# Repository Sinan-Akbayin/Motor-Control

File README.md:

# Motor-Control

KiCad hardware design for a three-phase BLDC motor drive, built around an STM32G473 microcontroller and a DRV8350S gate driver.

> **Status:** version 1.0.0. The schematic is finished (ERC: 0 errors) and the PCB is placed and routed (DRC: 0 errors, 0 unconnected items). No board has been built or tested yet. See [Known issues and open items](#known-issues-and-open-items).

The full schematic is also available as a PDF, so it can be viewed without KiCad: [docs/schematic.pdf](docs/schematic.pdf). In most PDF viewers you can click a sheet symbol to open that sheet.

To edit the design, open `BLDC_V_0.1/BLDC_V_0.1.kicad_pro` in KiCad 10 or newer. The `BLDC_V_0.1` file and folder names are kept from the upstream repository; they do not give the version. This repository holds the hardware design only; no firmware is included.

## Hardware overview

| Block | Parts | Notes |
|---|---|---|
| MCU | STM32G473VET6 | LQFP100, 24 MHz crystal |
| Gate driver | DRV8350S | SPI interface and enable line to the MCU; nFAULT goes to the TIM8 break input |
| Power stage | 6 × BSC070N10NS5SCATMA1 N-channel MOSFETs (PG-WSON-8) | Three half-bridges, 5 Ω gate resistors |
| Current sensing | 4 × AD8418A, 3 × 1.5 mΩ phase shunts, 1 × 1 mΩ DC bus shunt | Phase shunts between each half-bridge and its motor phase; bus shunt on the high side |
| Voltage sensing | 39 kΩ / 2.2 kΩ dividers | DC bus and all three phases |
| DC bus input | 30 A 58 VDC ATO fuse, 5.0SMDJ58A TVS (5 kW) | Overcurrent and overvoltage protection for a 48 V nominal bus |
| DC bus capacitors | 6 × Rubycon 100ZLJ220M12.5X25 (220 µF, 100 V, through-hole) | 1320 µF in total; together they carry about 12 A RMS of ripple current at 20 kHz, enough for 15 A RMS phase current |
| Power supply | LMR38020 buck, AMS1117-3.3 regulator | DC bus to 5 V, then 5 V to 3.3 V; a BAT54C diode-OR feeds the 3.3 V regulator from the 5 V rail or USB VBUS, so USB alone can power the 3.3 V logic (with little voltage margin, see changes.md) |
| CAN | ISO1050 isolated transceiver, B0505S-1WR2 isolated 5 V converter | ACM2012 choke and PESD2CAN ESD protection; a 240 Ω resistor gives the converter its minimum load |
| USB | Micro-B connector, USBLC6-2SC6 | ESD protection on D+ and D- |
| Temperature sensing | 10 kΩ NTC | On the board, plus an input for an external sensor on J10 |
| PCB | — | 4 copper layers, 98.5 × 84.3 mm, 1.6 mm thick (see [PCB](#pcb)) |

## Theoretical specifications

These values are calculated from datasheets. They have not been measured on a board yet. The design point is a 48 V bus, 20 kHz PWM, 40 °C ambient air and a MOSFET junction temperature of at most 110 °C.

| Parameter | Value | What limits it |
|---|---|---|
| Nominal input voltage | 48 V (13-cell Li-ion pack, 54.6 V when fully charged) | — |
| Input voltage range | 9 V to 58 V | Low end: DRV8350S supply, 9 V minimum. High end: the 58 V stand-off voltage of the TVS diode D5; above about 64 V the TVS starts to conduct |
| Absolute maximum bus voltage | 80 V, short transients only | DRV8350S VM pin (80 V absolute maximum) and AD8418A inputs (80 V survival). These are damage limits, not operating limits: the DRV8350S is specified up to 75 V and the AD8418A up to 70 V. At 80 V the bus voltage divider would also put 4.27 V on the MCU pin, above its 3.3 V supply |
| Continuous phase current | 15 A RMS without a heatsink (estimate, to be confirmed by a thermal test) | MOSFET heating: about 1.4 W per MOSFET with 50 K/W junction-to-air. The datasheet gives 50 K/W for a single MOSFET on a test board with 6 cm² of copper; six MOSFETs close together on this board may run hotter |
| Continuous phase current with a heatsink | about 18 A RMS | DC bus capacitor ripple current: 6 × 2.21 A at 100 kHz, about 12.2 A at 20 kHz |
| Peak phase current (short pulses) | ±50 A | Range of the phase current measurement. ±50 A gives 0.15 V to 3.15 V at the ADC; the motor-control firmware (not part of this repository) must set the over-current trip below this |
| DC input current | about 17 A at 15 A RMS phase current | 30 A fuse |
| Output power | about 0.8 kW at 48 V and 15 A RMS | Assumes space-vector PWM at full modulation, a power factor of 0.9, and no losses. With plain sine PWM it is about 0.7 kW |
| PWM frequency | 20 kHz (design point used for the numbers above) | Higher frequencies raise MOSFET switching losses |
| Phase current measurement | 30 mV/A, 1.65 V at 0 A, range about ±53 A | 1.5 mΩ shunt × AD8418A gain of 20. The ideal range is ±55 A (0 V to 3.3 V); the amplifier output cannot reach the supply rails exactly |
| DC bus current measurement | 20 mV/A, 1.65 V at 0 A, range about ±80 A | 1 mΩ shunt × AD8418A gain of 20 (ideal ±82.5 A) |
| DC bus voltage measurement | 0 V to 61.8 V for 0 V to 3.3 V at the ADC | 39 kΩ / 2.2 kΩ divider |
| Overvoltage clamp | about 80 V or less for surge currents up to about 21 A (rough estimate, not a guaranteed value) | 5.0SMDJ58A datasheet: at most 93.6 V at 53.5 A (10/1000 µs pulse). The datasheet gives no clamping voltage at lower currents |
| Interfaces | Isolated CAN, USB, UART, I2C, SPI, SWD, Hall sensors or encoder | — |

How the main numbers were found:

- **MOSFET heating.** BSC070N10NS5SCATMA1 on-resistance is at most 7.0 mΩ at 25 °C. At about 110 °C it is taken as 1.6 times higher, 11.2 mΩ (an estimate; read the exact factor from the datasheet curve). In a half-bridge, each MOSFET conducts about half of the time. At 15 A RMS one MOSFET loses 15² × 0.0112 / 2 = 1.26 W in conduction and about 0.15 W in switching (assuming 50 ns per switching edge; the real value depends on the gate drive current set in the DRV8350S). 1.4 W × 50 K/W = 70 K, so the junction reaches 40 + 70 = 110 °C.
- **Capacitor ripple.** In a three-phase inverter, the RMS ripple current in the DC bus capacitors can reach about 0.65 times the RMS phase current. At 15 A this is 9.8 A. Each capacitor is rated 2.21 A at 100 kHz and 105 °C (Rubycon ZLJ datasheet). At 20 kHz the rating is about 8 % lower, so six capacitors carry 6 × 2.21 × 0.92 ≈ 12.2 A.
- **TVS clamp.** At its rated pulse (53.5 A) the 5.0SMDJ58A clamps at 93.6 V. Its breakdown voltage is at most 71.2 V, measured at only 1 mA. Drawing a straight line between these two points gives a dynamic resistance is about (93.6 − 71.2) / 53.5 ≈ 0.42 Ω. The clamp stays at or below 80 V while the surge current is at most (80 − 71.2) / 0.42 ≈ 21 A. The real clamping curve is not a straight line, so this is only a rough estimate and not a guaranteed limit; check the protection against the surge waveform expected in use.

## Connectors

| Ref | Function |
|---|---|
| J14, J4 | DC bus power pads: VDC_IN (before the fuse) and GND |
| J5, J6, J7 | Motor phase pads: A, B and C |
| J13 | CAN bus: 1 CAN_H, 2 CAN_L, 3 isolated ground through 10 Ω |
| J12 | Jumper for the 120 Ω CAN termination: fit it across pins 2 and 3 (pin 1 is not connected) |
| J10 | 6-pin JST-EH for Hall sensors or an encoder (one at a time): 1 +5 V, 2 HA/A, 3 HB/B, 4 HC/Z (index), 5 external NTC, 6 GND |
| J2 | 10-pin SWD header with SWO and NRST |
| J1 | USB Micro-B |
| J3 | BOOT0 selection |
| J8 | UART, digital output DO_1 |
| J11 | I2C |
| J9 | External SPI |

## MCU pins

| Function | Pins |
|---|---|
| Gate driver high-side inputs A, B, C | PC6, PC7, PC8 |
| Gate driver low-side inputs A, B, C | PC10, PC11, PC12 |
| Gate driver SPI: CS, SCK, MISO, MOSI | PB12, PB13, PB14, PB15 |
| Gate driver enable, fault | PD15, PB7 (TIM8_BKIN) |
| Phase current A, B, C | PA1, PA3, PE7 (fast ADC channels, COMP1/2/4 inputs) |
| DC bus current | PA0 (fast ADC channel, COMP3 input) |
| Phase voltage A, B, C | PE14, PE15, PE13 |
| DC bus voltage | PA8 |
| Temperature: board, external | PC3, PC0 |
| Hall sensors / encoder A, B, C(Z) | PE2, PE3, PE4 (TIM3 CH1–CH3); C(Z) also on PD2 (TIM3_ETR) |
| CAN: RX, TX | PD0, PD1 |
| USB: D-, D+ | PA11, PA12 |
| SWD: SWDIO, SWCLK, SWO | PA13, PA14, PB3 |
| UART: RX, TX | PC4, PC5 |
| Digital output DO_1 | PB0 |
| I2C: SCL, SDA | PA15, PB9 |
| External SPI: CS, SCK, MISO, MOSI | PA4, PA5, PA6, PA7 |
| LEDs: CAN, process | PE5, PE1 |

## PCB

**Size.** 98.5 × 84.3 mm, rounded corners (1 mm radius), four M3 mounting holes. The power pads (DC input and motor phases) are on the bottom edge, the signal connectors on the top edge.

**Layer stack.** 4 copper layers, 1.6 mm total thickness, FR4:

| Layer | Copper | Use |
|---|---|---|
| F.Cu (top) | 70 µm (2 oz) | Parts, signal tracks, power copper areas |
| dielectric | 0.10 mm | — |
| In1.Cu | 35 µm (1 oz) | GND plane (kept out of the isolated CAN side) |
| dielectric (core) | 1.17 mm | — |
| In2.Cu | 35 µm (1 oz) | Power planes: VDC under the power stage, +5 V under the buck converter, +3.3 V under the MCU |
| dielectric | 0.10 mm | — |
| B.Cu (bottom) | 70 µm (2 oz) | Signal tracks, GND pour, part of the DC input copper |

**Netclasses** (in `BLDC_V_0.1.kicad_pro`; net names are assigned to classes by pattern):

| Netclass | Nets | Track width | Clearance | Via (pad / drill) |
|---|---|---|---|---|
| Default | everything not listed below | 0.20 mm | 0.20 mm | 0.6 / 0.3 mm |
| Power | DC bus, switch nodes, shunt nets | 0.50 mm | 0.25 mm | 0.8 / 0.4 mm |
| GateDrive | gate drive nets (DRV8350S to MOSFET gates) | 0.40 mm | 0.25 mm | 0.6 / 0.3 mm |
| Supply | GND, +5 V, +3.3 V, LDO_IN, VBUS and the converter nets | 0.40 mm | 0.20 mm | 0.6 / 0.3 mm |
| ISO | CAN bus and isolated-side nets | 0.30 mm | 0.20 mm | 0.6 / 0.3 mm |

The high-current paths (DC bus, switch nodes, motor phases) are copper areas, not tracks.

**Board-wide minimums** (board setup in `BLDC_V_0.1.kicad_pro`): track width 0.2 mm, clearance 0.15 mm, smallest hole 0.2 mm (the five thermal vias in the U5 DRV8350S footprint; every other via on the board is 0.6 / 0.3 mm or 0.8 / 0.4 mm), via diameter 0.6 mm, annular ring 0.13 mm (the netclass vias have 0.15 mm or more), hole-to-copper 0.25 mm, hole-to-hole 0.25 mm, copper-to-board-edge 0.3 mm. The custom rule file `BLDC_V_0.1.kicad_dru` lowers the pad-to-pad clearance to 0.15 mm only between pads of the same part, for U1 (MCU, 0.5 mm pin pitch, 0.195 mm between pads) and C28 (0201 capacitor, 0.18 mm between pads); the netclass clearances apply everywhere else.

## Fabrication outputs

Gerber, drill, BOM and position files are not in the repository. Generate them from `BLDC_V_0.1.kicad_pcb` in KiCad (*File → Fabrication Outputs*), and refill the copper areas (*Edit → Fill All Zones*) first.

## Known issues and open items

- The board has not been built or tested. All ratings above are calculated, not measured.
- The CAN isolation is functional isolation, not safety isolation. The isolating parts themselves have only about 0.9 mm between their pins, and the ground copper areas keep at least 2.6 mm from the isolated side (the closest other copper, a +5 V track, is 2.36 mm away). Do not rely on it to protect people from dangerous voltages.
- DRC reports 0 errors and 13 warnings. 3 are silkscreen warnings caused by footprint graphics. 10 say that a board footprint differs from its library copy (R15, R16, R20, R21, R25, R26, L3, U2, U4 and J1); the difference is 1 nm rounding in pads or graphics.
- The 3D body of F1 (fuse holder) is a close substitute, not the real part.
- Confirm the PCB stack-up with the intended fabricator.
- Check the TVS, MOSFET and capacitor numbers against the manufacturers' current datasheets before relying on them.
- The 3.3 V rail has little voltage margin. The AMS1117-3.3 (U2) needs at least 4.6 V at its input, but its input comes from +5 V or USB VBUS through the BAT54C diode D2, so in the worst case it gets only 4.2 to 4.5 V and the 3.3 V rail can sag. With typical part values the margin is about 0.25 V. Details in [changes.md](changes.md#power-supply).
- The isolated CAN supply can be slightly too high. The isolated converter U9 (B0505S-1WR2) is unregulated; with its minimum load it gives 5.25 V typical and up to 5.5 V worst case. The ISO1050 (U10) is specified for 4.75 to 5.25 V on VCC2, with 6 V absolute maximum. Measure VCC2 on the first board with the CAN bus idle. Details in [changes.md](changes.md#isolated-can).
- The TVS cannot absorb braking energy. If the battery is disconnected while the motor brakes, the bus voltage rises, so the motor-control firmware must limit or stop braking when the bus voltage gets too high.
- Local bus decoupling has not been tested. Each half-bridge has three ceramic capacitors from VDC to GND, 15 nF, 330 nF and 1 µF (C39, C40 and C42 on phase A), 5 to 9 mm from the MOSFETs (centre to centre). That is about 1.35 µF per phase. On the first board, measure the ringing on the switch nodes; if it is too high, add 100 V ceramic capacitance close to the MOSFETs.

## Repository layout

All design files are in [BLDC_V_0.1/](BLDC_V_0.1):

| File | Content |
|---|---|
| `BLDC_V_0.1.kicad_pro` | Main KiCad project file, including the netclasses and board design rules |
| `BLDC_V_0.1.kicad_sch` | Top-level schematic |
| `MCU_STM32.kicad_sch` | MCU, power pins, programming and USB |
| `DRV8350.kicad_sch` | Gate driver, buck converter, bulk capacitors, temperature and voltage measurement |
| `DC_Bus.kicad_sch` | DC bus input: fuse, TVS, bus current shunt and amplifier |
| `Half-Bridge.kicad_sch` | One half-bridge with its current and voltage sensing, used three times |
| `Communications.kicad_sch` | Connectors, isolated CAN, ESD protection |
| `BLDC_V_0.1.kicad_pcb` | PCB layout |
| `BLDC_V_0.1.kicad_dru` | Custom design rule (fine-pitch pad clearance, see [PCB](#pcb)) |
| `Libraries/` | Third-party symbols, footprints and 3D models |
| `BLDC_Project.pretty/` | Project footprint library: the 10 × 10 mm power pads, the MOSFET footprint (`Infineon_PG-WSON-8_BSC070N10NS5SC`) and the DRV8350S footprint (`TI_RTV0032E_DRV8350S`) |

Outside `BLDC_V_0.1/`:

| Path | Content |
|---|---|
| `docs/schematic.pdf` | The whole schematic as a PDF with clickable sheet links, exported from KiCad (*File → Plot*); export it again after any schematic change |
| `docs/render/` | 3D renders of the board used in this README |
| `changes.md` | Every change made since the upstream design, with the reason for each one |

The KiCad design files are written by KiCad 10.0. Open them with KiCad 10 or newer.

## Changes from version 0.1

Version 1.0.0 fixes errors in the version 0.1 schematic and replaces the PCB layout. In short:

- Power rails fixed: the 3.3 V rail was split across two unconnected nets, and the buck converter had no feedback.
- USB VBUS separated from the 5 V rail; a diode-OR lets USB power the 3.3 V logic.
- MCU pins reassigned so that the fast ADC channels, comparators, the TIM8 break input and TIM3 (Hall sensors or encoder) can be used.
- New DC bus input: fuse, larger TVS, bus current measurement. Bulk capacitors changed to 100 V parts with enough ripple current rating.
- Isolated CAN corrected (bus capacitors, minimum load for the isolated converter); Hall/encoder connector given supply pins.
- All parts renumbered, so the reference designators do not match the upstream schematic.
- PCB redone from scratch: 4 layers, new outline, placed and routed by script.

[changes.md](changes.md) lists every change and the reason for it.

## Licence

Copyright Sinan Akbayin 2023.

The design files are licensed under the CERN Open Hardware Licence Version 2 - Permissive ([CERN-OHL-P-2.0](LICENSE)). The design is provided without any warranty.

Source location: <https://github.com/Sinan-Akbayin/Motor-Control>

The contents of `BLDC_V_0.1/Libraries/` come from third parties and are not covered by this licence. They remain subject to their own licence terms.

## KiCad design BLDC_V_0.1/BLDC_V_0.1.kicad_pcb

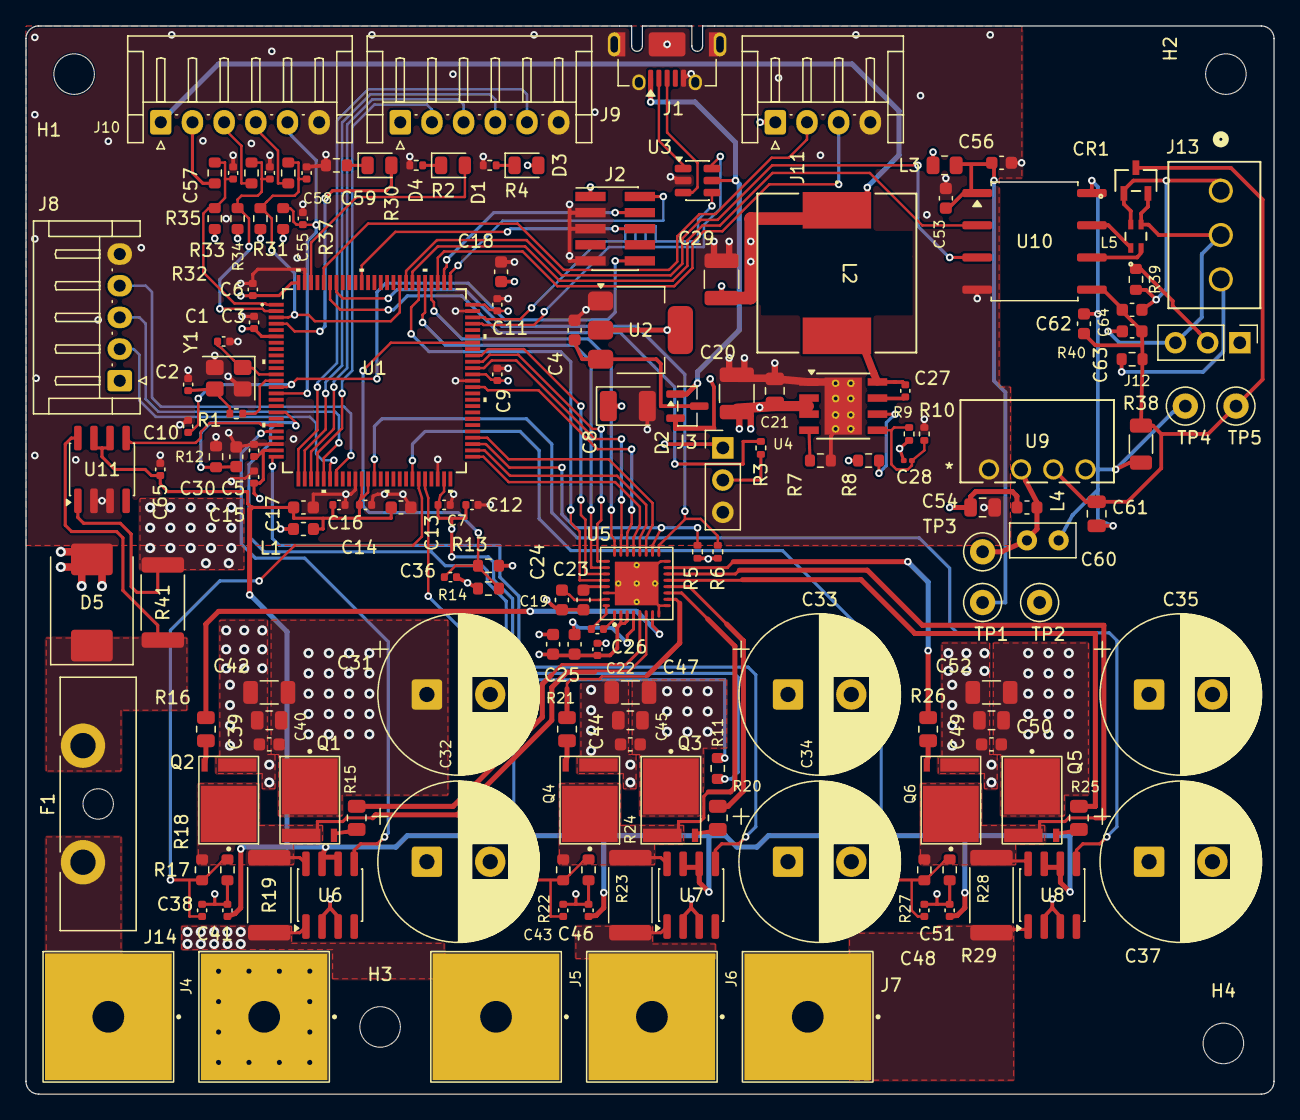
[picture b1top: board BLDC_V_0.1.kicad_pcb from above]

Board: 4 copper layers, 98.5 x 84.3 mm, 159 parts (0 on the bottom side), 104 nets.

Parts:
C1, C2: 20p; C_0402_1005Metric
C3, C5, C6, C7, C9, C10, C11, C12, C14, C15, C16, C22, C27, C36, C38, C41, C43, C46, C48, C51, C65: 100n; C_0402_1005Metric
C4: 4u7; C_0603_1608Metric
C8: 22u; CP_EIA-3528-21_Kemet-B
C13, C23, C24, C25: 1u; C_0603_1608Metric
C17, C18, C19: 10u; C_0603_1608Metric
C20: 2.2u; C_1210_3225Metric
C21: 100n; C_0805_2012Metric
C26: 47n; C_0402_1005Metric
C28: 56p; C_0201_0603Metric
C29: 47u; C_1210_3225Metric
C30: 2.2u; C_0603_1608Metric
C31, C32, C33, C34, C35, C37: 220u; CP_Radial_D12.5mm_P5.00mm
C39, C44, C49: 15n; C_0603_1608Metric
C40, C45, C50: 330n; C_0805_2012Metric
C42, C47, C52: 1u; C_1206_3216Metric
C53: 10n; C_0603_1608Metric
C54, C61: 2.2u; C_0805_2012Metric
C55, C57, C58, C59: 4.7n; C_0402_1005Metric
C56, C62: 100n; C_0603_1608Metric
C60: 470p; C_Disc_D5.0mm_W2.5mm_P2.50mm
C63, C64: 100p; C_0603_1608Metric
CR1: PESD2CAN_215; SOT23_TO-236AB_NEX
D1: BLUE; LED_0805_2012Metric
D2: BAT54C; SOT-23
D3, D4: RED; LED_0805_2012Metric
D5: 5.0SMDJ58A; D_SMC
F1: 30A 58VDC ATO; Fuseholder_Blade_ATO_Littelfuse_Pudenz_2_Pin
H1, H2, H3, H4: MountingHole; MountingHole_3.2mm_M3
J1: USB_B_Micro; USB_Micro-AB_Molex_47590-0001
J2: SWD; PinHeader_2x05_P1.27mm_Vertical_SMD
J3, J12: Conn_01x03; PinHeader_1x03_P2.54mm_Vertical
J4: GND; Power_Welding_Pad_10x10mm
J5, J6, J7: Phase; Power_Welding_Pad_10x10mm
J8: Conn_01x05; JST_EH_S5B-EH_1x05_P2.50mm_Horizontal
J9: Conn_01x06; JST_EH_S6B-EH_1x06_P2.50mm_Horizontal
J10: HALL/ENC; JST_EH_S6B-EH_1x06_P2.50mm_Horizontal
J11: Conn_01x04; JST_EH_S4B-EH_1x04_P2.50mm_Horizontal
J13: 15EDGVC-3.5-03P-14-00AH; CONN_15EDGVC-3.5-03P-1X_DEG
J14: VDC_IN; Power_Welding_Pad_10x10mm
L1: BLM18PG221SN1D; L_0603_1608Metric
L2: CDRH127/LDNP-470MC; IND_CDRH127&slash_LDNP-470MC_SUM
L3: 0R5; R_0805_2012Metric
L4: 4.7u; L_0603_1608Metric
L5: ACM2012-900-2P-T002; ACM2012_TDK
Q1, Q2, Q3, Q4, Q5, Q6: BSC070N10NS5SCATMA1; Infineon_PG-WSON-8_BSC070N10NS5SC
R1: 47R; R_0402_1005Metric
R2: 1k5; R_0402_1005Metric
R3, R6, R10: 10k; R_0402_1005Metric
R4: 1k; R_0402_1005Metric
R5: 4.7k; R_0402_1005Metric
R7: 64k9; R_0603_1608Metric
R8: 100k; R_0603_1608Metric
R9: 40.2k; R_0402_1005Metric
R11: NTC 10k; R_0603_1608Metric
R12, R31, R32, R33, R34: 10k; R_0603_1608Metric
R13, R17, R22, R27: 39k; R_0603_1608Metric
R14, R18, R23, R28: 2k2; R_0603_1608Metric
R15, R16, R20, R21, R25, R26: 5R; R_0805_2012Metric
R19, R24, R29: 0.0015R; R_2512_6332Metric
R30: 470; R_0603_1608Metric
R35, R36, R37: 100; R_0603_1608Metric
R38: 240; R_1206_3216Metric
R39: 120; R_0603_1608Metric
R40: 10; R_0603_1608Metric
R41: 1m 3W; R_2512_6332Metric
TP1, TP2, TP3, TP4, TP5: TestPoint; TestPoint_Loop_D1.80mm_Drill1.0mm_Beaded
U1: STM32G473VET6; LQFP100-14x14mm
U2: AMS1117-3.3; SOT-223-3_TabPin2
U3: USBLC6-2SC6; SOT-23-6
U4: LMR38020SDDAR; TI_SO-PowerPAD-8_ThermalVias
U5: DRV8350SRTVT; TI_RTV0032E_DRV8350S
U6, U7, U8, U11: AD8418A; SOIC-8_3.9x4.9mm_P1.27mm
U9: B0505S-1WR2; B0505S-1WR2_MNS
U10: ISO1050DUB; SOP-8_6.62x9.15mm_P2.54mm
Y1: 24MHz; Crystal_SMD_3225-4Pin_3.2x2.5mm

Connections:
5V_ISO: C60.2, C61.1, C62.2, R38.1, TP4.1, U9.4, U10.8
+3.3V: C3.1, C5.1, C6.1, C7.1, C8.1, C9.1, C11.1, C12.1, C15.1, C18.1, D3.2, J2.1, J3.1, J8.1, J9.1, J11.1, L1.1, L3.1, R5.1, R6.1, R11.1, R31.1, R32.1, R33.1, R34.1, U1.6, U1.24, U1.49, U1.64, U1.75, U1.100, U2.2
+3.3VA: C13.1, C14.1, C16.1, C17.1, C41.1, C46.1, C51.1, C65.1, L1.2, U1.36, U1.37, U6.6, U6.7, U7.6, U7.7, U8.6, U8.7, U11.6, U11.7
+5V: C28.1, C29.1, C54.1, D2.2, J10.1, L2.1, L4.1, R8.1, R9.1
/Communications/CAN_LED: D4.2, U1.4
/Communications/CAN_RX: U1.82, U10.2
/Communications/CAN_TX: U1.83, U10.3
/Communications/DO_1: J8.4, U1.32
/Communications/EXT_SPI_CS: J9.5, U1.26
/Communications/EXT_SPI_MISO: J9.3, U1.28
/Communications/EXT_SPI_MOSI: J9.2, U1.29
/Communications/EXT_SPI_SCK: J9.4, U1.27
/Communications/HALL_A: C57.1, R32.2, R35.2, U1.1
/Communications/HALL_B: C58.1, R33.2, R36.2, U1.2
/Communications/HALL_C: C59.1, R34.2, R37.2, U1.3, U1.84
/Communications/I2C_SCL: J11.3, U1.78
/Communications/I2C_SDA: J11.2, U1.96
/Communications/TEMP_IN: C55.1, J10.5, R31.2, U1.15
/Communications/UART_1_RX: J8.3, U1.30
/Communications/UART_1_TX: J8.2, U1.31
/DRV8350/DRV_CS: U1.51, U5.21
/DRV8350/DRV_ENABLE: U1.62, U5.22
/DRV8350/FAULT_N: R6.2, U1.94, U5.17
/DRV8350/GHA: R15.1, U5.5
/DRV8350/GHB: R20.1, U5.12
/DRV8350/GHC: R25.1, U5.13
/DRV8350/GLA: R16.1, U5.7
/DRV8350/GLB: R21.1, U5.10
/DRV8350/GLC: R26.1, U5.15
/DRV8350/INHA: U1.65, U5.23
/DRV8350/INHB: U1.66, U5.25
/DRV8350/INHC: U1.67, U5.27
/DRV8350/INLA: U1.79, U5.24
/DRV8350/INLB: U1.80, U5.26
/DRV8350/INLC: U1.81, U5.28
/DRV8350/PCB_TEMP: C30.1, R11.2, R12.1, U1.18
/DRV8350/SENS_VDC: C36.1, R13.1, R14.2, U1.69
/DRV8350/SHA: Q1.S, Q2.D, R17.2, R19.1, U5.6, U6.8
/DRV8350/SHB: Q3.S, Q4.D, R22.2, R24.1, U5.11, U7.8
/DRV8350/SHC: Q5.S, Q6.D, R27.2, R29.1, U5.14, U8.8
/DRV8350/SPI_MISO: R5.2, U1.53, U5.18
/DRV8350/SPI_MOSI: U1.54, U5.19
/DRV8350/SPI_SCK: U1.52, U5.20
BOOT0: R3.2, U1.95
CAN_H: C64.2, CR1.1, J13.1, L5.4, R39.1
CAN_L: C63.1, CR1.2, J12.3, J13.2, L5.3
CURR_A: U1.21, U6.5
CURR_B: U1.25, U7.5
CURR_C: U1.38, U8.5
GND: C1.2, C2.2, C3.2, C4.2, C5.2, C6.2, C7.2, C8.2, C9.2, C10.2, C11.2, C12.2, C13.2, C14.2, C15.2, C16.2, C17.2, C18.2, C19.2, C20.2, C21.2, C22.2, C23.1, C24.1, C29.2, C30.2, C31.2, C32.2, C33.2, C34.2, C35.2, C36.2, C37.2, C38.2, C39.2, C40.2, C41.2, C42.2, C43.2, C44.2, C45.2, C46.2, C47.2, C48.2, C49.2, C50.2, C51.2, C52.2, C53.2, C54.2, C55.2, C56.2, C57.2, C58.2, C59.2, C65.2, D5.2, J1.5, J1.SH, J2.3, J2.5, J2.9, J3.3, J4.1, J8.5, J9.6, J10.6, J11.4, Q2.S, Q4.S, Q6.S, R2.1, R4.1, R7.2, R10.2, R12.2, R14.1, R18.1, R23.1, R28.1, R30.1, TP2.1, U1.23, U1.35, U1.48, U1.63, U1.74, U1.99, U2.1, U3.2, U4.1, U4.9, U5.8, U5.9, U5.16, U5.30, U5.33, U6.2, U6.3, U7.2, U7.3, U8.2, U8.3, U9.1, U10.4, U11.2, U11.3, Y1.2, Y1.4
GND_ISO: C61.2, C62.1, C63.2, C64.1, CR1.3, R38.2, R40.2, TP5.1, U9.3, U10.5
HSE_IN: C1.1, U1.12, Y1.1
HSE_OUT: R1.1, U1.13
I_DC: U1.20, U11.5
LDO_IN: C4.1, D2.3, U2.3
NRST: C10.1, J2.10, U1.14
unnamed: C2.1, R1.2, Y1.3
unnamed: D1.1, R2.2
unnamed: D3.1, R4.2
unnamed: D4.1, R30.2
unnamed: J3.2, R3.1
unnamed: J10.2, R35.1
unnamed: J10.3, R36.1
unnamed: J10.4, R37.1
unnamed: J12.2, R39.2
unnamed: J13.3, R40.1
unnamed: Q1.G, R15.2
unnamed: Q2.G, R16.2
unnamed: Q3.G, R20.2
unnamed: Q4.G, R21.2
unnamed: Q5.G, R25.2
unnamed: Q6.G, R26.2
unnamed: C27.1, U4.7
unnamed: C28.2, R9.2, R10.1, U4.5
unnamed: R8.2, U4.6
unnamed: R7.1, U4.4
unnamed: C27.2, L2.2, U4.8
unnamed: C26.1, U5.1
unnamed: C26.2, U5.32
unnamed: C23.2, U5.29
unnamed: C25.2, U5.4
unnamed: C24.2, U5.31
unnamed: J5.1, R19.2, U6.1
unnamed: J6.1, R24.2, U7.1
unnamed: J7.1, R29.2, U8.1
unnamed: C60.1, L4.2, TP3.1, U9.2
unnamed: L5.1, U10.7
unnamed: L5.2, U10.6
unnamed: C53.1, C56.1, L3.2, TP1.1, U10.1
PROCCESS_LED: D1.2, U1.98
SENS_A: C38.1, R17.1, R18.2, U1.45
SENS_B: C43.1, R22.1, R23.2, U1.46
SENS_C: C48.1, R27.1, R28.2, U1.44
SWCLK: J2.4, U1.77
SWDIO: J2.2, U1.76
SWO: J2.6, U1.90
USB_CONN_D+: J1.3, U3.3
USB_CONN_D-: J1.2, U3.1
USB_D+: U1.73, U3.4
USB_D-: U1.72, U3.6
VBUS: D2.1, J1.1, U3.5
VDC: C19.1, C20.1, C21.1, C22.1, C25.1, C31.1, C32.1, C33.1, C34.1, C35.1, C37.1, C39.1, C40.1, C42.1, C44.1, C45.1, C47.1, C49.1, C50.1, C52.1, Q1.D, Q3.D, Q5.D, R13.2, R41.2, U4.2, U4.3, U5.2, U5.3, U11.1
VDC_F: D5.1, F1.2, R41.1, U11.8
VDC_IN: F1.1, J14.1

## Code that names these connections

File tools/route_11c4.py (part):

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  batch A  north-west of the MCU: LED cathodes, J10 -> hall series resistors, HALL_A/B/C, TEMP_IN,
           CAN_LED, HSE crystal
  batch B  DRV bus (SPI, INHx, INLx, DRV_ENABLE, FAULT_N)
  batch C  south pins, NRST, BOOT0, PCB_TEMP + R11, north-pin bus (PROCCESS_LED, I2C, CAN), SWD, USB, VBUS
  (the plan below is the original one; batch D = supplies, GND vias, isolated CAN side, buck feedback)

Plan for the rest (not drawn yet)
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           (CURR_C / SENS_C lanes). Exit vias, two rows: LC (143.0,130.8) HC (143.8,130.0)
           LB (144.6,130.8) HB (145.4,130.0) LA (146.2,130.8) HA (147.0,130.0) EN (147.8,130.8);
           F.Cu stubs: lanes x 143.8/144.2/144.6/145.0 into U5 pins 28..25, straight into 24..22.
           FAULT_N: pin 17 -> north -> east -> R6 pad 2 as a loop that encloses R5; MISO reaches
           R5 pad 2 through its own via (153.0,131.3) and pin 18 through a via at (149.6,131.2).
  SENS_VDC the 11c3 F.Cu track along x 138.9 walls off the east pins: replace it with a stub under
           the body (pin 69 west along y 117.0 to a via at 126.6,117.0), B.Cu south along x 126.6,
           east along y 130.4, via (135.7,132.0), F.Cu down to R13 pad 1
  under-body vias also for NRST (pin 14), PCB_TEMP (pin 18), BOOT0, I2C_SDA, PROCCESS_LED
  then     south pins (EXT_SPI, UART, DO_1), SWD, USB, I2C_SCL, CAN_RX/TX, buck feedback, LDO,
           isolated CAN side, +3.3VA and +5V branches, GND / +3.3V vias, F.Cu GND pour north of
           y 133 (not on the isolated side) as the last step
"""
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    t('HALL_C', [(118.5, 106.38), (119.0, 105.88), (119.48, 105.4), (121.2, 105.4), (121.51, 105.09),
                 (121.51, 104.08), (122.15, 104.08)], WP)
    t('HALL_C', [(121.51, 104.08), (121.51, 102.78), (120.7, 102.78)], WP)
    # MCU pin 1 (HALL_A): through the gap between C6 and C3, then north-west to R32 pad 2
    t('HALL_A', [(119.75, 114.0), (119.0, 114.0), (118.9, 113.9), (116.45, 113.9), (114.0, 111.45),
                 (114.0, 106.8), (114.42, 106.38), (114.9, 106.38)], WP)
    # MCU pin 2 (HALL_B): same gap, then a B.Cu hop under HALL_A to the lane between R33 and R34
    t('HALL_B', [(119.75, 114.5), (118.85, 114.5), (118.67, 114.32), (115.3, 114.32)], WP)
    v('HALL_B', 115.3, 114.32)
    t('HALL_B', [(115.3, 114.32), (115.3, 112.0), (117.6, 109.7), (117.6, 109.4)], W, 'B')
    v('HALL_B', 117.6, 109.4)
    t('HALL_B', [(117.6, 109.4), (117.6, 107.2), (117.1, 106.7), (116.7, 106.38)], WP)
    # MCU pins 3 and 84 (both HALL_C) joined under the body; B.Cu from a via on that link to the
    # lane between R34 and R31
    # (the link runs south of the under-body vias of FAULT_N / BOOT0, north of the CAN_LED via)
    t('HALL_C', [(119.75, 115.0), (120.7, 115.0), (121.2, 114.8), (122.3, 114.8), (122.8, 115.3), (128.8, 115.3),
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    t('INHA', [(147.0, 129.4), (147.0, 132.2), (146.95, 132.6), (146.95, 133.6)], WP)
    t('DRV_ENABLE', [(147.8, 130.2), (147.8, 131.3), (147.45, 132.0), (147.45, 133.6)], WP)

    # --- FAULT_N: MCU pin 94 -> F.Cu east under the body (over the EXT_SPI / NRST B.Cu lanes) -> via
    # -> B.Cu under the north pins, through the gap, south-east to a via north of R5/R6; F.Cu loop
    # pin 17 -> R6 pad 2 around the MISO vias
    t('FAULT_N', [(124.5, 112.25), (124.5, 113.0), (125.0, 113.5), (128.6, 113.5)], WP)
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# ------------------------------------------------------------------------------------ batch C
def south_pins(B):
    """MCU south pins 26-32. EXT_SPI: F.Cu north under the body to two via rows, B.Cu straight north
    (x 124.55..125.75) under the north pins to J9, entering the pins from the north side. UART / DO_1:
    F.Cu fan to the north-east, vias, B.Cu west in the band y 122.05..122.85 to J8."""
    t, v = B.track, B.via
    for net, xp, ya, xv, yv, xl, yd, yr, xj in (
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        v(net, xv, yv)
        t(net, [(xv, yv), (xv, yd), (xl, yd - (xl - xv)), (xl, yr + 0.4), (xl + 0.4, yr), (xj - 0.4, yr),
                (xj, yr + 0.4), (xj, 99.6)], WP, 'B')
    # UART_1_RX (pin 30), UART_1_TX (31), DO_1 (32)
    t('UART_1_RX', [(123.5, 127.75), (123.5, 126.1), (124.7, 124.9)], WP)
    v('UART_1_RX', 124.7, 124.9)
    t('UART_1_TX', [(124.0, 127.75), (124.0, 126.575), (124.3, 126.275)], WP)
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
def pcb_temp(B):
    t, v = B.track, B.via
    # pin 18 -> via under the body -> B.Cu: west to R12 / C30, and south between the CURR_A / CURR_B lanes
    t('PCB_TEMP', [(119.75, 122.5), (120.5, 122.5), (121.3, 123.3), (121.3, 123.55)], WP)
    v('PCB_TEMP', 121.3, 123.55)
    t('PCB_TEMP', [(121.3, 123.55), (121.05, 123.3), (119.8, 123.3), (114.6, 123.3), (113.8, 124.1),
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

def north_bus(B):
    """North pins on F.Cu. PROCCESS_LED to D1.2 at y 105.5. I2C / CAN: lanes N->S SDA 107.6, CAN_TX 108.9,
    CAN_RX 109.35, SCL 109.8 (north of C18 and of the SWCLK via), south-east into the corridor between J2
    and U2 (y 111.25 .. 112.54), north between J2 and C29 (x 150.0 .. 151.35), east south of U3
    (y 106.85 .. 108.2, south of the USB_D+ via), north-east between U3 and the +5V corner, east north of L2
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    t(PG, [(167.32, 127.3), (167.9, 126.7), (167.9, 123.3), (168.6, 122.64)], W, 'B')
    v(PG, 168.6, 122.64)
    t(PG, [(168.6, 122.64), (167.2, 122.64)], W)
    # LDO_IN: C4.1 -> U2.3 -> under the U2 tab -> x 150.1 between C8 and D2 -> between D2 pins 1/2 -> D2.3
    t('LDO_IN', [(143.3, 116.78), (143.3, 117.0), (143.9, 118.3), (145.35, 118.3), (149.75, 118.3),
                 (150.1, 118.65), (150.1, 122.0), (153.14, 122.0)], 0.3)
    # D2.2 (+5V) round the south and east of D2.3 to a via in the In2 +5V zone
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
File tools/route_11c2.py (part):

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    # thermal vias of the buck's exposed pad: solid, a relief has no room for its spokes there
    B.zone('GND', 'B', [(162.4, 119.1), (166.6, 119.1), (166.6, 124.9), (162.4, 124.9)], prio=1, solid=True,
           clearance=0.25, name='GND_B_U4')
    # In2: VDC under the band + tongue up to the buck input (C20, C21, U4 pins 2-3)
    # ... and a notch up to y 128.9 on the left for the via array of R41 pad 2
    B.zone('VDC', 'In2', [(100, 128.9), (117.0, 128.9), (117.0, 133.2), (154.2, 133.2), (154.2, 120.8), (163.0, 120.8), (163.0, 133.2),
                          (173.4, 133.2), (175.54, 138.56), (180.7, 140.7), (198.5, 140.7), (198.5, 176.3), (100, 176.3)],
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    B.zone('VDC_F', 'F', [(101.6, 140.3), (112.7, 140.3), (112.7, 146.0), (107.5, 146.0), (107.5, 150.8),
                          (101.6, 150.8)], prio=2, name='VDC_F')
    # R41 pad 2 -> In2 VDC plane: F.Cu patch north and east of the pad + 17 vias (20 A, ~1.2 A each)
    B.zone('VDC', 'F', [(109.0, 129.3), (117.2, 129.3), (117.2, 134.9), (109.0, 134.9)], prio=2,
           name='VDC_R41')
    B.vias('VDC', [109.8, 111.4, 113.0, 114.6, 116.2], [130.0, 131.6, 133.2])
    B.vias('VDC', [114.2, 116.0], [134.4 - 0.0])
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# ------------------------------------------------------------------------------------ gate drive
def gate_drive(B):
    t = B.track
    # --- phase A: U5 south pins 5 (GHA), 6 (SHA), 7 (GLA)
    # pair GHA/SHA: under the DRV caps, down between C31/C32 column and bridge B, then west between
    # the two bulk caps into R15 (keeps Q1 drain <-> C31 joined on F.Cu)
    t('GHA', [(148.45, 138.4), (148.45, 141.3), (147.35, 142.40), (140.75, 142.40), 0.4,
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    B.via('GLA', 139.8, 138.2)
    t('GLA', [(139.8, 138.2), (114.55, 138.2), (114.2, 138.55), (114.2, 146.59)], 0.4)

    # --- phase B: U5 east pins 12 (GHB), 11 (SHB), 10 (GLB)
    t('GHB', [(150.6, 136.25), (156.27, 136.25), (156.62, 136.6), 0.4, (156.62, 153.24),
              (156.27, 153.59), (154.6, 153.59)], 0.24)
    t('SHB', [(150.6, 136.75), (155.6, 136.75), (155.95, 137.1), 0.4, (155.95, 152.1),
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              (151.25, 143.34), (145.45, 143.34), (145.24, 143.55), (143.05, 143.55), (142.7, 143.9),
              (142.7, 144.3), 0.4, (142.7, 146.59)], 0.24)

    # --- phase C: U5 east pins 13 (GHC), 14 (SHC), 15 (GLC)
    t('GHC', [(150.6, 135.75), (156.5, 135.75), (156.63, 135.62), 0.4, (165.83, 135.62), (170.16, 139.95),
              (184.4, 139.95), (184.4, 153.59), (183.1, 153.59)], 0.24)
    t('SHC', [(150.6, 135.25), (156.0, 135.25), (156.3, 134.95), 0.4, (166.4, 134.95), (170.75, 139.3),
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
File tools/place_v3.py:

"""Placement v3 for BLDC_V_0.1 = placement v2 with the control section re-planned around the MCU pins.

usage (KiCad's bundled Python, KiCad closed or on a copy):
  python place_v3.py place <in.kicad_pcb> <out.kicad_pcb>
  python place_v3.py check <board.kicad_pcb> [ref.kicad_pcb]

Why v3 (see docs/WORK.md, step 11b3). STM32G473 LQFP100 pin groups, by package side:
  side 1 (pins 1-25):   HALL, HSE, NRST, TEMP, I_DC, CURR_A, CURR_B
  side 2 (pins 26-50):  EXT_SPI, UART, DO, CURR_C, SENS_C/A/B
  side 3 (pins 51-75):  DRV SPI, DRV_ENABLE, INHx, SENS_VDC, USB
  side 4 (pins 76-100): SWD, I2C, INLx, CAN, FAULT, BOOT0, LEDs
v2 used MCU rotation 270 (side 1 north, side 2 west): every analog pin faced away from the power
stage and USB faced away from its connector. v3 uses rotation 0: side 1 west, side 2 south (analog
toward the power band), side 3 east (DRV, USB), side 4 north (SWD, I2C, CAN).

Unchanged from v2: board outline, power band (bridges, bulk caps, pads), input column, DRV8350S
cluster, buck cluster, isolated CAN cluster, mounting holes, J1, J2, J8, J11, U3.
"""
import os
import sys

sys.path.insert(0, os.path.dirname(os.path.abspath(__file__)))
import place_v2 as v2  # noqa: E402

MCU_C = (127.5, 120.0)
MCU_ROT = 0
J10_X, J9_X = 110.64, 129.54        # swapped: HALL connector above the MCU's west side (pins 1-3)
PHASE_PAD_X = (137.1, 149.4, 161.7)  # J5, J6, J7
LDO_DX = 2.5                       # LDO group moved east: keeps x 138.3..142.5 free for INLx/FAULT


def build_table():
    v2.MCU_C, v2.MCU_ROT = MCU_C, MCU_ROT
    t = _v2_table()
    # connectors: HALL/ENC left, EXT_SPI right (reached on B.Cu from MCU side 2; JST pins are THT)
    t['J10'] = (J10_X, v2.CONN_Y, 0)
    t['J9'] = (J9_X, v2.CONN_Y, 0)
    # hall / temp input filters under J10, same arrangement as v2 relative to the connector
    x0 = J10_X + 4.26
    for i, r in enumerate(['R35', 'C57', 'R36', 'C58', 'R37', 'C59']):
        t[r] = (x0 + 1.45 * i, 103.6, 90)
    for i, r in enumerate(['R32', 'R33', 'R34', 'R31']):
        t[r] = (x0 + 1.8 * i, 107.2, 90)
    t['C55'] = (x0 + 6.95, 107.2, 90)
    # LDO group east of the MCU->DRV corridor
    t.update({'U2': (146.0 + LDO_DX, 116.0, 0), 'C4': (140.8 + LDO_DX, 116.0, 90),
              'C8': (147.5, 122.0, 0), 'D2': (152.2, 122.0, 0)})
    # boot jumper out of the space north of the DRV8350S control pins (BOOT0 is a static level)
    t.update({'J3': (155.0, 125.3, 0), 'R3': (158.0, 125.3, 90)})
    # LEDs in one row under J9, north of the MCU; leaves y 104..111 free for the side-4 fan-out
    # resistor left of its LED: resistor pad 2 and LED pad 1 (cathode net) face each other
    for r, x in (('R30', 124.5), ('D4', 127.9), ('R2', 130.8), ('D1', 133.7), ('R4', 136.6), ('D3', 139.5)):
        t[r] = (x, 103.0, 0)
    # SENS_VDC divider south-east of the MCU, between its bypass caps and bulk cap C31
    t.update({'R13': (136.5, 134.6, 0), 'R14': (136.5, 136.4, 0), 'C36': (133.5, 135.5, 0)})
    # bottom edge (user 2026-11-11): supply group VDC_IN, GND | mounting hole H3 | motor group A, B, C
    # at one pitch (12.3 mm, the same as VDC_IN -> GND). H3 sits in the gap between the two groups.
    t.update({'J5': (PHASE_PAD_X[0], v2.PAD_Y, 0), 'J6': (PHASE_PAD_X[1], v2.PAD_Y, 0),
              'J7': (PHASE_PAD_X[2], v2.PAD_Y, 0), 'H3': (127.95, 171.0, 0)})
    return t


_v2_table = v2.build_table
v2.build_table = build_table

if __name__ == '__main__':
    if sys.argv[1] == 'place':
        v2.place(sys.argv[2], sys.argv[3])
    else:
        v2.check(sys.argv[2], sys.argv[3] if len(sys.argv) > 3 else None)

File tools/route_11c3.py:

"""Step 11c3 for BLDC_V_0.1: analog nets on top of the 11c2 copper, by explicit coordinates.

usage (KiCad's bundled Python, KiCad closed or on a copy):
  python route_11c3.py <route_11c2.kicad_pcb> <out.kicad_pcb>

The input must be the output of tools/route_11c2.py; nothing is removed, only tracks and vias are
added and the zones are refilled. All coordinates are board mm (x right, y down).

Nets: CURR_A/B/C (AD8418A outputs U6/U7/U8 -> MCU), I_DC (U11 -> MCU), SENS_A/B/C (phase voltage
dividers -> MCU), SENS_VDC (bus divider -> MCU).

Layer use: F.Cu runs lie over the unbroken In1 GND plane. Long runs through the power band are on
B.Cu, below In1 GND and In2 VDC, in the lanes between the bridges or under the DC (VDC) islands,
not under a switch-node zone. The MCU pins of CURR_A/B/C and SENS_C are boxed in by bypass
capacitors, so they go to a via under the MCU body.

Same temp-folder handling as route_11c2.py (pcbnew's Save() rewrites the .kicad_pro next to it).
"""
import os
import shutil
import sys
import tempfile

sys.path.insert(0, os.path.dirname(os.path.abspath(__file__)))
from route_11c2 import Board, PITCH, sh  # noqa: E402

W = 0.25          # analog track
WP = 0.2          # at 0.5 mm pitch MCU pins and between 0603 pads


def curr(B):
    t, v = B.track, B.via
    # amplifier output (pin 5) -> via north-east of the amplifier, same shape on each bridge
    for k, net in enumerate(('CURR_A', 'CURR_B', 'CURR_C')):
        dx = k * PITCH
        t(net, sh([(128.3, 156.0), (127.75, 156.55), (126.4, 156.55), (125.905, 157.05), (125.905, 158.125)], dx), W)
        v(net, 128.3 + dx, 156.0)

    # CURR_A / CURR_B: MCU pins 21 / 25 leave on the outer (west) side to vias next to the pin row, so
    # that F.Cu and B.Cu under the south-west corner of the body stay free for the south pins 26-32
    # (11c4). B.Cu lanes south: CURR_A x 117.0, CURR_B x 119.45; x 117.6 between them is PCB_TEMP (11c4).
    t('CURR_A', [(119.75, 124.0), (119.0, 124.0), (118.55, 124.15)], WP)
    v('CURR_A', 118.55, 124.15)
    t('CURR_A', [(118.55, 124.15), (117.0, 125.7), (117.0, 132.9), (118.1, 134.0), (126.6, 134.0), (128.6, 136.0),
                 (128.6, 155.7), (128.3, 156.0)], W, 'B')

    # CURR_B: via in the free corner between pins 25 and 26, B.Cu south, east along y 133, down the
    # A/B lane, under the DRV caps and the VDC island of bridge B, then down east of bridge B
    t('CURR_B', [(119.75, 126.0), (119.45, 126.0), (119.45, 126.75)], WP)
    v('CURR_B', 119.45, 126.75)
    t('CURR_B', [(119.45, 126.75), (119.45, 132.45), (120.0, 133.0), (137.4, 133.0), (137.4, 135.5), (138.9, 137.0),
                 (138.9, 142.0), (139.5, 142.6), (157.0, 142.6), (157.6, 143.2), (157.6, 155.2),
                 (156.8, 156.0)], W, 'B')

    # CURR_C: MCU pin 38 -> via under the body -> B.Cu east out of the MCU, north of U5, north of
    # bridge C, down east of bridge C
    t('CURR_C', [(127.5, 127.75), (127.5, 126.2)], WP)
    v('CURR_C', 127.5, 126.2)
    t('CURR_C', [(127.5, 126.2), (127.5, 123.6), (128.1, 123.0), (139.5, 123.0), (141.5, 125.0), (141.5, 130.4),
                 (143.5, 132.4), (170.5, 132.4), (172.9, 134.8), (172.9, 139.3), (173.5, 139.9), (185.5, 139.9),
                 (186.1, 140.5), (186.1, 155.2), (185.3, 156.0)], W, 'B')


def i_dc(B):
    # U11 pin 5 -> MCU pin 20, F.Cu: between R1 and the GND via of C30, then between C10 and R12
    B.track('I_DC', [(119.75, 123.5), (118.6, 123.5), (118.44, 123.34), (114.5, 123.34), (113.8, 124.04),
                     (113.8, 124.5), (113.4, 124.9), (108.3, 124.9), (107.905, 124.525)], WP)


def sens(B):
    t, v = B.track, B.via
    # divider tap: R18 pad 2 -> R17 pad 1 -> C38 pad 1, and a via west of the cluster
    for k, net in enumerate(('SENS_A', 'SENS_B', 'SENS_C')):
        dx = k * PITCH
        t(net, sh([(115.9, 157.775), (115.45, 157.95), (114.4, 159.0), (113.9, 159.425)], dx), WP)
        t(net, sh([(111.4, 159.4), (113.9, 159.4)], dx), W)
        t(net, sh([(112.9, 159.4), (112.9, 162.28), (113.9, 162.28)], dx), WP)
        v(net, 111.4 + dx, 159.4)

    # SENS_A: MCU pin 45 -> F.Cu south between C13 and C7, west below the MCU caps, via, B.Cu west
    # of bridge A
    # (the two jogs are steep, 0.25 over 0.75 mm, so the parallel diagonals keep 0.27 mm between them)
    t('SENS_A', [(131.0, 127.75), (131.0, 128.5), (131.25, 129.25), (131.25, 132.3), (130.55, 133.0),
                 (119.6, 133.0), (118.4, 134.2), (118.4, 135.8)], WP)
    v('SENS_A', 118.4, 135.8)
    t('SENS_A', [(118.4, 135.8), (112.4, 135.8), (111.4, 136.8), (111.4, 159.4)], W, 'B')

    # SENS_B: MCU pin 46 -> F.Cu south next to SENS_A, via above the GLA track, B.Cu down the A/B lane
    t('SENS_B', [(131.5, 127.75), (131.5, 128.5), (131.75, 129.25), (131.75, 137.0)], WP)
    v('SENS_B', 131.75, 137.0)
    # x 138.5: clear of the through-hole pad 2 of C32 (bulk capacitor)
    t('SENS_B', [(131.75, 137.0), (138.5, 143.75), (138.5, 158.0), (139.9, 159.4)], W, 'B')

    # SENS_C: MCU pin 44 -> via under the body -> B.Cu east inside CURR_C, down the B/C lane
    t('SENS_C', [(130.5, 127.75), (130.5, 126.3)], WP)
    v('SENS_C', 130.5, 126.3)
    t('SENS_C', [(130.5, 126.3), (130.5, 125.0), (131.5, 124.0), (139.0, 124.0), (140.5, 125.5), (140.5, 130.9),
                 (143.0, 133.4), (166.5, 133.4), (167.5, 134.4), (167.5, 158.5), (168.4, 159.4)], W, 'B')


def sens_vdc(B):
    t = B.track
    # R13 pad 1 - R14 pad 2 (diagonal between the four pads), C36 pad 1 along the top
    t('SENS_VDC', [(135.675, 134.6), (135.9, 134.9), (137.1, 136.1), (137.325, 136.4)], WP)
    t('SENS_VDC', [(133.02, 135.5), (133.02, 134.6), (135.675, 134.6)], WP)
    # -> MCU pin 69. A track east of the MCU would wall off the east pins (DRV bus, USB), so the pin
    # goes west under the body to a via, B.Cu south (west of CURR_C) and east below the MCU caps,
    # and comes up next to R13
    t('SENS_VDC', [(135.25, 117.0), (128.8, 117.0), (126.6, 119.2)], WP)
    B.via('SENS_VDC', 126.6, 119.2)
    t('SENS_VDC', [(126.6, 119.2), (126.6, 129.9), (127.1, 130.4), (134.1, 130.4), (135.7, 132.0)], W, 'B')
    B.via('SENS_VDC', 135.7, 132.0)
    t('SENS_VDC', [(135.7, 132.0), (135.675, 134.6)], WP)


def main(src, dst):
    dst = os.path.abspath(dst)
    stem = os.path.splitext(dst)[0]
    with tempfile.TemporaryDirectory() as tmp:
        work = os.path.join(tmp, os.path.basename(dst))
        shutil.copyfile(src, work)
        for ext in ('.kicad_pro', '.kicad_dru'):
            if os.path.exists(stem + ext):
                shutil.copyfile(stem + ext, os.path.splitext(work)[0] + ext)
            else:
                print('warning: no', stem + ext, '- zone fill uses default rules')
        B = Board(work)
        curr(B)
        i_dc(B)
        sens(B)
        sens_vdc(B)
        B.fill_and_save(work)
        shutil.copyfile(work, dst)
    print('added', B.count)


if __name__ == '__main__':
    main(sys.argv[1], sys.argv[2])

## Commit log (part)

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2023-08-06 First commit.
2023-08-06 SPI pull-up check is done.
2023-08-06 Xtal changed 16MHz to 24MHz.
2023-08-06 MCU VDD-VDDA-VREF pins checked and components added.
2023-08-06 MCU ADC allocation is done.
2023-08-06 .gitignore added.
2023-08-11 Connectors and CAN circuit added.
2023-08-11 Schematic prototip done.
2023-12-03 PCB placement completed.
